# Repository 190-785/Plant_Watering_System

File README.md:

# Plant Watering System 🌱💧

An automated irrigation system using ESP8266 microcontrollers with soil moisture monitoring and intelligent watering control. Available in two versions: Basic IO and WiFi-enabled.

> **Part of the BloomWatch ecosystem.** This firmware repo is one half of a two-repo project. The ESP8266 WiFi module collects soil moisture data and pushes it to Firebase Firestore, where the companion **[BloomWatch Web App](https://github.com/190-785/bloomwatch-webapp)** picks it up to display real-time dashboards, historical charts, and remote watering controls.

## Overview

This project consists of two main components with increasing levels of functionality:

### 1. IO Module (Basic Version)
A standalone irrigation controller that:
- Monitors soil moisture levels using an analog sensor
- Automatically controls a water pump based on moisture thresholds
- Provides real-time serial monitoring of system status
- Uses simple threshold-based logic for pump control

### 2. WiFi Module (Advanced Version)
An enhanced version with networking and cloud capabilities that includes:
- All basic irrigation functionality from the IO module
- WiFi connectivity with web-based configuration portal
- Firebase/Firestore integration for cloud data synchronization
- Real-time data synchronization to the cloud
- Remote configuration and control via Firebase
- Historical data logging and analytics
- Device-specific data paths using MAC address
- Web dashboard integration capabilities
- Data logging and remote monitoring capabilities
- Web server for system status and configuration
- JSON-based configuration management
- Button controls and LED status indicators
- Pump safety features and fault detection

## Hardware Requirements

### Core Components
- **Microcontroller**: ESP8266 (NodeMCU v2/v3)
- **Moisture Sensor**: Analog soil moisture sensor
- **Water Pump**: Small DC water pump (5V/12V)
- **Pump Driver**: ULN2003 or similar relay/driver circuit
- **Power Supply**: Appropriate for your pump voltage

### WiFi Version Additions
- **Push Button**: Momentary push button for manual controls
- **Status LED**: Single LED for status indication
- **WiFi Network**: 2.4GHz WiFi network for connectivity

### Wiring
- **Pump Control**: GPIO D1 (Pin 5) → ULN2003 IN1
- **Moisture Sensor**: A0 (Analog pin) → Sensor output
- **Button** (WiFi/Firebase): GPIO D2 (Pin 4) → Button + pull-up resistor
- **LED** (WiFi/Firebase): GPIO D3 (Pin 0) → LED anode
- **Power**: 3.3V/5V and GND connections as required

## Project Structure

```
Plant_Watering_System/
├── IO/                     # Basic irrigation system
│   ├── platformio.ini     # PlatformIO configuration
│   ├── src/
│   │   └── main.cpp       # Main irrigation logic
│   ├── include/           # Header files
│   └── lib/               # Local libraries
│
├── Wifi/                   # WiFi-enabled version
│   ├── platformio.ini     # PlatformIO configuration with WiFi libs
│   ├── src/
│   │   ├── main.cpp       # Main application with WiFi
│   │   ├── Config.cpp/h   # Configuration management
│   │   ├── ProvisionServer.cpp/h  # WiFi provisioning
│   │   └── PortalLogin.cpp/h      # Web portal authentication
│   ├── include/           # Header files
│   ├── lib/               # Local libraries
│   ├── HARDWARE_GUIDE.md  # Detailed hardware setup
│   ├── QUICK_REFERENCE.md # Quick reference card
│   ├── TESTING_MANUAL.md  # Manual testing procedures
│   └── TESTING_SIMULATION.md # Simulation testing guide
│
├── .gitignore             # Git ignore rules
├── LICENSE                # Project license
└── README.md              # This file
```

## Getting Started

### Prerequisites
- [PlatformIO IDE](https://platformio.org/platformio-ide) or [PlatformIO Core](https://platformio.org/install/cli)
- ESP8266 development board (NodeMCU recommended)
- Basic electronics components listed above

### Installation

1. **Clone the repository**:
   ```bash
   git clone https://github.com/190-785/Plant_Watering_System.git
   cd Plant_Watering_System
   ```

2. **Choose your version**:
   - For basic functionality: Navigate to `IO/` directory
   - For WiFi features: Navigate to `Wifi/` directory

3. **Build and upload**:
   ```bash
   # For basic version
   cd IO
   pio run --target upload

   # For WiFi version
   cd Wifi
   pio run --target upload
   ```

4. **Monitor serial output**:
   ```bash
   pio device monitor
   ```

### Configuration

#### Basic Version (IO)
- Power on the device near your plant
- Insert the moisture sensor into the soil
- Position the water pump in your water reservoir
- The system will automatically maintain optimal soil moisture

#### WiFi Version
1. **Initial Setup**: On first boot, the device creates a WiFi access point
2. **Connect**: Join the AP and navigate to the configuration portal
3. **Configure WiFi**: Set WiFi credentials and system parameters
4. **Firebase Setup** (Optional): Create a Firebase project and enable Firestore
5. **Configure Firebase** (Optional): Update `firebaseProjectId`, `firebaseApiKey`, and `firebaseDatabaseURL` in the code
6. **Deploy**: The system will connect to your network and begin operation, with optional cloud sync

## Features by Version

| Feature | IO | WiFi |
|---------|----|------|
| Moisture monitoring | ✅ | ✅ |
| Automatic watering | ✅ | ✅ |
| Serial monitoring | ✅ | ✅ |
| Web interface | ❌ | ✅ |
| WiFi connectivity | ❌ | ✅ |
| Button controls | ❌ | ✅ |
| LED status | ❌ | ✅ |
| Pump safety | ❌ | ✅ |
| Data logging | ❌ | ✅ |
| Remote monitoring | ❌ | ✅ |
| Cloud sync | ❌ | ✅ |
| Historical data | ❌ | ✅ |

## Thresholds and Timing

### Moisture Control Logic
- **Dry Threshold**: 480-520 (triggers pump activation)
- **Wet Threshold**: 420-440 (stops pump operation)
- **Pump Runtime**: 1-2 seconds per cycle
- **Wait Period**: 1-2 minutes between pump cycles

### WiFi Version Features
- **Button Controls**: Triple-press (WiFi reset), Long-press (clear fault), Short-press (manual water)
- **LED Patterns**: 8 different status indicators
- **Web Endpoints**: Dashboard, status JSON, manual controls
- **Safety Features**: Pump interval enforcement, fault detection
- **Firebase Integration**: Real-time cloud synchronization, historical data logging
- **Device ID**: Auto-generated from MAC address
- **Data Paths**: `plantData/{deviceId}/` structure
- **Collections**: Live status, historical logs, remote config, commands
- **Sync Intervals**: Status every 10s, config check every 30s

## Documentation

### WiFi Version Documentation
- **[HARDWARE_GUIDE.md](Wifi/HARDWARE_GUIDE.md)** - Complete hardware setup and wiring
- **[QUICK_REFERENCE.md](Wifi/QUICK_REFERENCE.md)** - Quick reference card for controls and commands
- **[TESTING_MANUAL.md](Wifi/TESTING_MANUAL.md)** - Manual testing procedures and checklists
- **[TESTING_SIMULATION.md](Wifi/TESTING_SIMULATION.md)** - Simulation testing guide

## Customization

### Adjusting Thresholds
Modify the constants in `main.cpp`:
```cpp
constexpr uint16_t DRY_THRESHOLD = 520;  // Your dry value
constexpr uint16_t WET_THRESHOLD = 420;  // Your wet value
```

### Timing Adjustments
```cpp
const unsigned long PUMP_RUN_TIME = 1000;    // Pump duration (ms)
const unsigned long PUMP_WAIT_TIME = 60000;  // Wait between cycles (ms)
```

### WiFi Version Configuration
- **Portal Timeout**: 5 minutes for configuration
- **WiFi Retry**: Smart exponential backoff (1h → 6h → 24h)
- **Data Logging**: Every 30 seconds when online

### Firebase Configuration (WiFi Version)
Update these values in the WiFi version for cloud features:
```cpp
String firebaseProjectId = "your-project-id";
String firebaseApiKey = "your-api-key";
String firebaseDatabaseURL = "your-database-url";
```

## Troubleshooting

### Common Issues
- **Pump not activating**: Check wiring and power supply
- **Erratic readings**: Ensure sensor is properly inserted in soil
- **WiFi connection fails**: Verify credentials and signal strength
- **Continuous pumping**: Check sensor calibration and thresholds
- **Firebase sync fails**: Verify project credentials and permissions

### Version-Specific Issues

#### WiFi Version
- **Portal not appearing**: Triple-press button to force portal mode
- **LED not responding**: Check polarity (long leg to D3, short leg to GND)
- **Button not working**: Verify D2 connection and pull-up resistor
- **Firebase sync fails**: Check Firebase credentials and network connectivity
- **Device not appearing in Firebase**: Verify Firestore security rules
- **Firebase commands not working**: Check device ID format and collection paths

### Debugging
- Enable serial monitoring for detailed system status
- Check sensor readings manually with multimeter
- Verify pump operation with direct power connection
- Use the testing guides in the WiFi documentation

## Contributing

1. Fork the repository
2. Create a feature branch (`git checkout -b feature/amazing-feature`)
3. Commit your changes (`git commit -m 'Add amazing feature'`)
4. Push to the branch (`git push origin feature/amazing-feature`)
5. Open a Pull Request

## License

This project is licensed under the terms specified in the LICENSE file.

## Acknowledgments

- Built using PlatformIO and Arduino framework
- Designed for ESP8266 microcontrollers
- Inspired by the need for automated plant care solutions
- Firebase integration using Firebase Arduino Client Library

## Companion Web App

**Repository:** [github.com/190-785/bloomwatch-webapp](https://github.com/190-785/bloomwatch-webapp)

The WiFi version of this firmware writes sensor data and pump status to Firebase Firestore under `plantData/{deviceId}`. The BloomWatch web app reads that same Firestore path to provide:

- **Real-time dashboard** — live moisture levels, pump status, connection state
- **Historical charts** — moisture trends over 24h / 7d / 30d
- **Remote control** — water now, clear faults, adjust thresholds from anywhere
- **Multi-device management** — monitor multiple plants from one interface
- **User authentication** — secure, role-based access

### How they connect

```
ESP8266 Firmware (this repo)        BloomWatch Web App
─────────────────────────────       ──────────────────────
Reads soil moisture sensor    ──►   Displays live readings
Controls water pump           ◄──   Sends waterNow / clearFault commands
Pushes logs to Firestore      ──►   Renders historical charts
Pulls config from Firestore   ◄──   Lets users adjust thresholds
```

Both repos share the same Firebase project (`bloom-watch-d6878`) and Firestore data structure. See the [BloomWatch README](https://github.com/190-785/bloomwatch-webapp#readme) for web app setup.

---

**Happy Growing! 🌱**

*Choose your version based on your needs:*
- **IO**: Simple, reliable, offline operation
- **WiFi**: Network connectivity, remote monitoring, and optional cloud features

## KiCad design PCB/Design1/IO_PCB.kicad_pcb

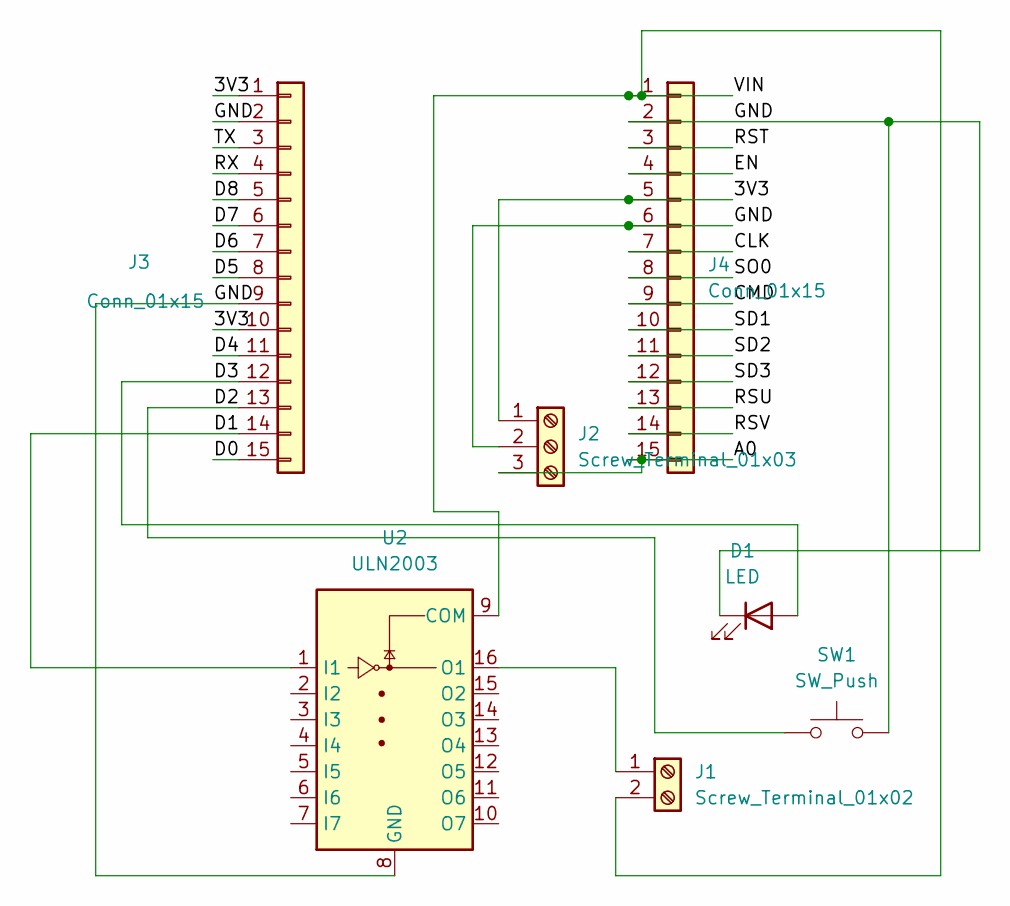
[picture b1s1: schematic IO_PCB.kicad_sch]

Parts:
D1: LED; LED_D5.0mm
J1: Screw_Terminal_01x02; PinHeader_1x02_P2.54mm_Vertical
J2: Screw_Terminal_01x03; PinHeader_1x03_P2.54mm_Vertical
J3, J4: Conn_01x15; PinHeader_1x15_P2.54mm_Vertical
SW1: SW_Push; SW_PUSH-12mm
U2: ULN2003; DIP-16_W7.62mm

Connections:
/3V3: J2.1, J3.1, J3.10, J4.5
/A0: J2.3, J4.15
/CLK: J4.7
/CMD: J4.9
/D0: J3.15
/D1: J3.14, U2.1 (I1)
/D2: J3.13, SW1.1
/D3: D1.2 (A), J3.12
/D4: J3.11
/D5: J3.8
/D6: J3.7
/D7: J3.6
/D8: J3.5
/EN: J4.4
/GND: D1.1 (K), J2.2, J3.2, J3.9, J4.2, J4.6, SW1.2, U2.8 (GND)
/RST: J4.3
/RSU: J4.13
/RSV: J4.14
/RX: J3.4
/SD1: J4.10
/SD2: J4.11
/SD3: J4.12
/SO0: J4.8
/TX: J3.3
/VIN: J1.2, J4.1, U2.9 (COM)
unnamed: J1.1, U2.16 (O1)

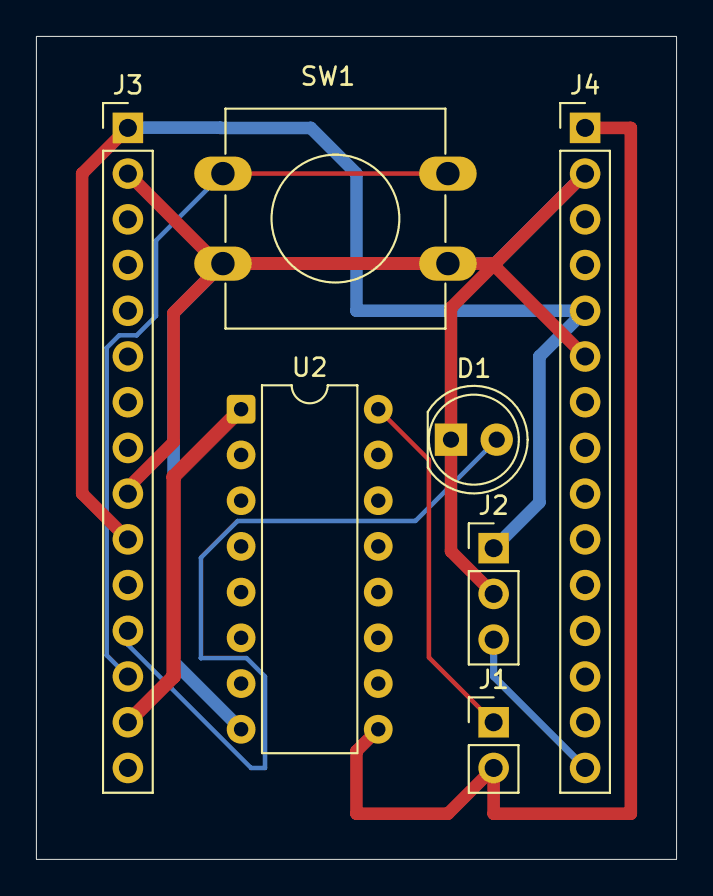
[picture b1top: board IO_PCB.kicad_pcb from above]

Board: 2 copper layers, 35.6 x 45.7 mm, 7 parts (0 on the bottom side), 8 nets.

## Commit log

2025-06-23 Added Gitignore and Readme File
2025-07-21 Updated the code
2025-07-22 Firebase addded
2025-07-23 Revoked the key main.cpp
2025-08-01 Updated firebase
2025-08-01 Firebase full integration done
2025-08-02 Connected app device
2025-08-24 Add offline-first logic and manual pump control
    Refactored main loop to support offline-first operation, enabling core irrigation logic and status display without WiFi. Added manual pump activation via button, LED status indicators for system and 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
2025-10-28 Add Phase 1 docs and update config for ESP8266
    Added comprehensive documentation: HARDWARE_GUIDE.md, PHASE1_IMPLEMENTATION.md, QUICK_REFERENCE.md, and README_DEPLOYMENT.md for the Smart Irrigation System. Updated platformio.ini with correct libra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
2025-10-28 Add manual and simulation test plans and Wokwi diagram
    Added comprehensive manual and simulation testing guides for the Smart Irrigation System, including hardware and software checklists, test suites, and result templates. Included Wokwi simulation diag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
2025-10-28 Improve serial output and Firestore logging
    Enhanced serial output formatting for button presses, pump activation, and effectiveness checks to improve readability. Updated Firestore logging to include additional device metrics such as WiFi RSS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
2025-10-28 Update Firebase config and remote command handling
    Changed Firebase API key and added database URL. Improved remote command processing by clearing individual fields (clearFault, waterNow) using PATCH requests instead of deleting the document, and add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
2025-10-28 Use Firebase server timestamp for lastSeen field
    Replaces the ESP8266 epoch time with Firebase's server timestamp for the lastSeen field in device status updates. This ensures more accurate and consistent time tracking across devices.
2025-10-29 Improve triple and short press detection logic
    Refactored button press handling to immediately detect triple presses on the third press and delay short press detection until the triple press window expires. This prevents short presses from being 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
2025-10-29 Speed up testing and improve NTP sync logging
    Reduced delays and intervals for faster testing, including setting MIN_INTERVAL_SEC to 0 and shortening pump settle time. Enhanced NTP time synchronization feedback with detailed timestamp output and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
2025-11-02 Update Firebase credentials in main.cpp
    Replaced the Firebase API key and database URL with placeholders, as the previous credentials have been revoked.
2025-11-02 Update README and main.cpp; remove deployment docs
    Expanded README.md with detailed feature matrix, hardware, and configuration instructions for both IO and WiFi versions. Deleted Wifi/PHASE1_IMPLEMENTATION.md and Wifi/README_DEPLOYMENT.md to consoli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
2025-11-06 Update config defaults and remove testing overrides
    Changed configuration parameter defaults to production values and removed code that forcibly set MIN_INTERVAL_SEC to 0 for testing. Updated comments and serial output to clarify configuration via Fir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
2025-12-19 Adjust pump logic and Firestore sync for stability
    Reduced MIN_INTERVAL_SEC to 30s, increased MAX_NO_EFFECT_REPEATS to 10, and extended PUMP_SETTLE_MS to 20s for improved reliability. Firestore sync and status updates now occur even in LOCKED_FAULT s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
2025-12-19 Add initial Design1 PCB files and backups
    Added KiCad PCB, schematic, project, and related files for Design1, including IO board, Gerber outputs, DRC report, and multiple backup archives. This commit establishes the initial hardware design a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
2026-02-13 FIxed readme and connected the webapp
